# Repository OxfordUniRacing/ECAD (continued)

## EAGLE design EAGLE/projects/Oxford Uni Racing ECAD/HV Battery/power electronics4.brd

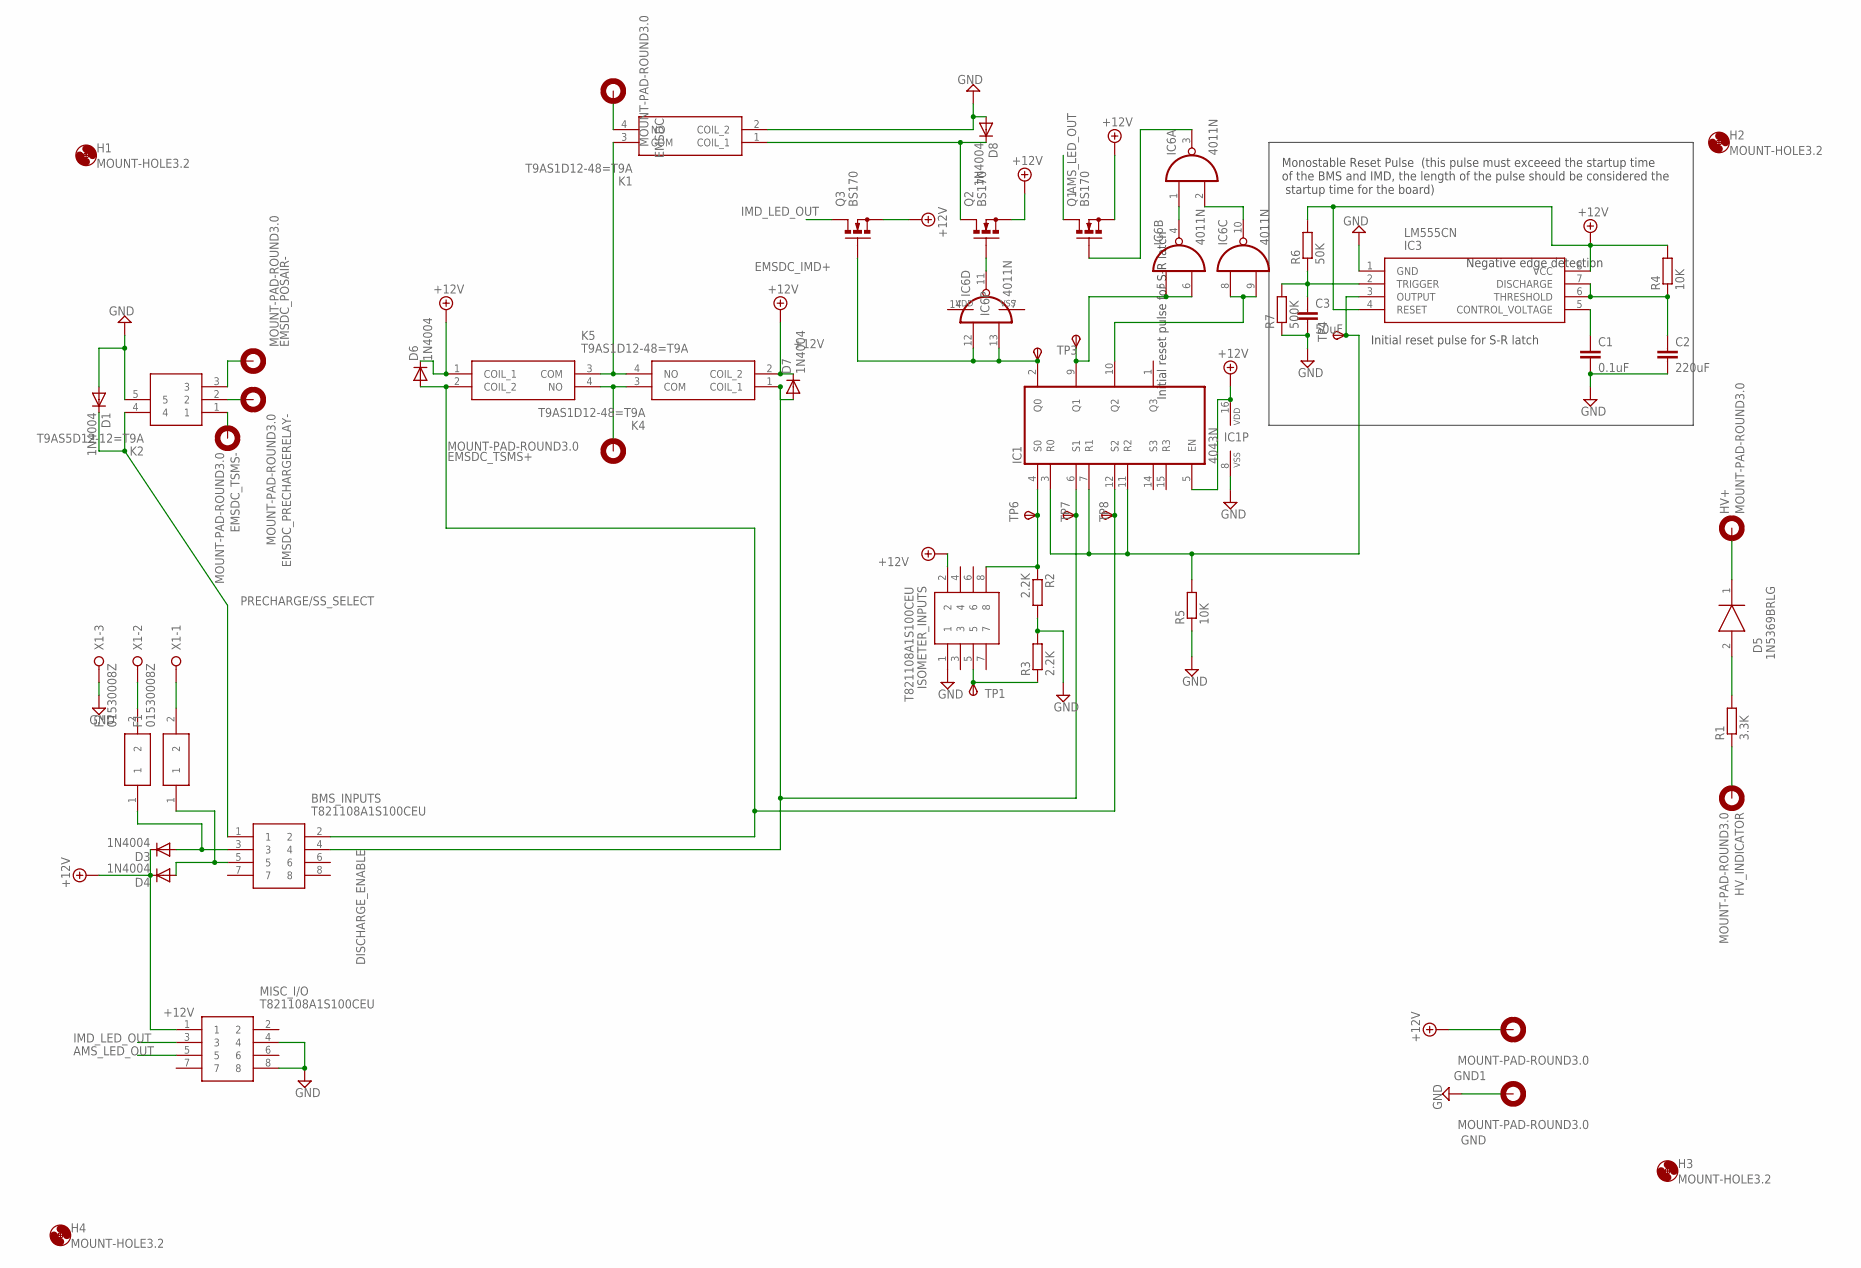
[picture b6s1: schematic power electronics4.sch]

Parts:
BMS_INPUTS: T821108A1S100CEU; HDRV8W64P254_2X4_1778X895X915P
C1: 0.1uF; C050-024X044
C2: 220uF; C050-024X044
C3: 50uF; C050-024X044
D1, D3, D4, D6, D7, D8: 1N4004; DO41-10
D5: 1N5369BRLG; DIOAD2260W109L864D349
EMSDC: MOUNT-PAD-ROUND3.0; 3,0-PAD
EMSDC_POSAIR-: MOUNT-PAD-ROUND3.0; 3,0-PAD
EMSDC_PRECHARGERELAY-: MOUNT-PAD-ROUND3.0; 3,0-PAD
EMSDC_TSMS+: MOUNT-PAD-ROUND3.0; 3,0-PAD
EMSDC_TSMS-: MOUNT-PAD-ROUND3.0; 3,0-PAD
F1, F2: 01530008Z; 01530008
GND, GND1: MOUNT-PAD-ROUND3.0; 3,0-PAD
H1, H2, H3, H4: MOUNT-HOLE3.2; 3,2
HV+: MOUNT-PAD-ROUND3.0; 3,0-PAD
HV_INDICATOR: MOUNT-PAD-ROUND3.0; 3,0-PAD
IC1: 4043N; DIL16
IC3: LM555CN; DIP762W53P254L980H533Q8N
IC6: 4011N; DIL14
ISOMETER_INPUTS: T821108A1S100CEU; HDRV8W64P254_2X4_1778X895X915P
K1, K4, K5: T9AS1D12-48=T9A; T9AS1D1248T9A
K2: T9AS5D12-12=T9A; T9AS1D12
MISC_I/O: T821108A1S100CEU; HDRV8W64P254_2X4_1778X895X915P
Q1, Q2, Q3: BS170; SOT54E
R1: 3.3K; 0207/15
R2, R3: 2.2K; 0207/12
R4, R5: 10K; 0207/15
R6: 50K; 0207/15
R7: 500K; 0207/15
TP1, TP2, TP3, TP4, TP6, TP7, TP8: TPSPAD1-17; P1-17
X1: W237-3E

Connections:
+12V: D3.C, D4.C, D6.C, D7.C, GND1.B3,0, IC1.5 (EN), IC1.16 (VDD), IC3.4 (RESET), IC3.8 (VCC), ISOMETER_INPUTS.2, K4.2 (COIL_2), K5.1 (COIL_1), MISC_I/O.1, Q1.S, Q2.S, Q3.S, R4.2, R6.2
AMS_LED_OUT: MISC_I/O.5, Q1.D
CHG_SAFE: BMS_INPUTS.2, D6.A, IC1.12 (S2), K5.2 (COIL_2), TP8.TP
DISCHARGE_ENABLE: BMS_INPUTS.4, D7.A, IC1.6 (S1), K4.1 (COIL_1), TP7.TP
EMSDC_IMD+: K1.3 (COM), K4.4 (NO), K5.3 (COM)
GND: C1.2, C2.2, C3.2, D1.A, D8.A, GND.B3,0, IC1.8 (VSS), IC3.1 (GND), ISOMETER_INPUTS.1, K1.2 (COIL_2), K2.5, MISC_I/O.4, MISC_I/O.8, R2.2, R3.2, R5.1, R7.1, X1.3
IMD_LED_OUT: MISC_I/O.3, Q3.D
unnamed: EMSDC_TSMS-.B3,0, K2.1
unnamed: EMSDC_POSAIR-.B3,0, K2.3
unnamed: EMSDC_PRECHARGERELAY-.B3,0, K2.2
unnamed: EMSDC_TSMS+.B3,0, K4.3 (COM), K5.4 (NO)
unnamed: D5.1 (K), HV+.B3,0
unnamed: BMS_INPUTS.3, D3.A, F2.1
unnamed: D5.2 (A), R1.2
unnamed: BMS_INPUTS.5, D4.A, F1.1
unnamed: HV_INDICATOR.B3,0, R1.1
unnamed: ISOMETER_INPUTS.5, R3.1, TP1.TP
unnamed: IC1.3 (R0), IC1.7 (R1), IC1.11 (R2), IC3.3 (OUTPUT), R5.2, TP4.TP
unnamed: IC1.9 (Q1), IC6.5 (I0), IC6.6 (I1), TP3.TP
unnamed: IC1.10 (Q2), IC6.8 (I0), IC6.9 (I1)
unnamed: IC6.1 (I0), IC6.4 (O)
unnamed: D8.C, K1.1 (COIL_1), Q2.D
unnamed: EMSDC.B3,0, K1.4 (NO)
unnamed: IC1.4 (S0), ISOMETER_INPUTS.8, R2.1, TP6.TP
unnamed: C2.1, IC3.6 (THRESHOLD), IC3.7 (DISCHARGE), R4.1
unnamed: C1.1, IC3.5 (CONTROL_VOLTAGE)
unnamed: IC6.2 (I1), IC6.10 (O)
unnamed: IC6.3 (O), Q1.G
unnamed: C3.1, IC3.2 (TRIGGER), R6.1, R7.2
unnamed: F2.2, X1.2
unnamed: F1.2, X1.1
unnamed: IC1.2 (Q0), IC6.12 (I0), IC6.13 (I1), Q3.G, TP2.TP
unnamed: IC6.11 (O), Q2.G
PRECHARGE/SS_SELECT: BMS_INPUTS.1, D1.C, K2.4
VDD: IC6.14 (VDD)
VSS: IC6.7 (VSS)

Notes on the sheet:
Negative edge detection
Initial reset pulse for S-R latch
Monostable Reset Pulse (this pulse must exceeed the startup time of the BMS and IMD, the length of the pulse should be considered the startup time for the board)

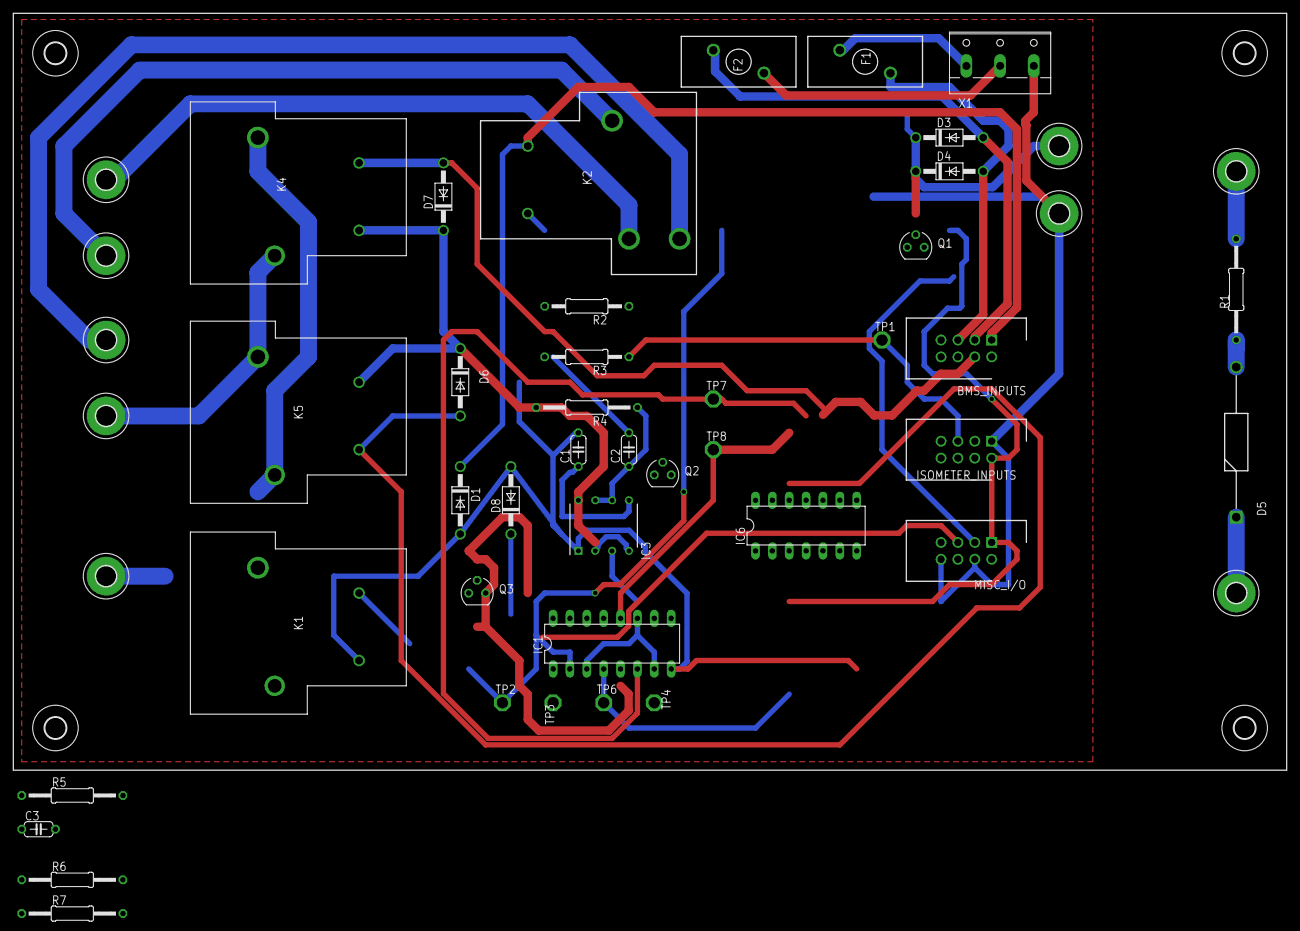
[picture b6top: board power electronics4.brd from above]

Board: 2 copper layers, 191.8 x 114.0 mm, 53 parts (0 on the bottom side), 34 nets.

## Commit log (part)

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2018-12-14 On branch master Initial commit Changes to be committed: new file: cam/DESCRIPTION new file: design blocks/DESCRIPTION new file: design rules/DESCRIPTION new file: design rules/default.dru new file: 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
2018-12-14 On branch master Your branch is up to date with 'origin/master'.
    Changes to be committed:
    new file: EAGLE/cam/DESCRIPTION
    new file: EAGLE/design blocks/DESCRIPTION
    new file: EAGLE/design rules/DESCRIPTION
    new file: EAGLE/design rules/default.dru
    new file: EAGLE/libraries/512-LM2903N-pcb-part-libraries/512-LM2903N-pcb-part-libraries.epw
2018-12-14 On branch master Your branch is up to date with 'origin/master'.
    Changes to be committed:
    deleted: cam/DESCRIPTION
    deleted: design blocks/DESCRIPTION
    deleted: design rules/DESCRIPTION
    deleted: design rules/default.dru
    deleted: libraries/512-LM2903N-pcb-part-libraries/512-LM2903N-pcb-part-libraries.epw
2018-12-15 Backlink to CADLAB.io has been added.
2018-12-15 Start new branch, for AMD/IMS schematic
2018-12-15 addition of libraries and slight update to IMD_AMS_Latch.sch
2018-12-19 Updates to BOTS circuit moving 12v pin to correct position and AMS circuit updates, including library for dual coil relay
2018-12-22 AMS/IMD readme updated
2019-01-03 Schematic and board design of driver switch interlock
2019-01-03 BOTS revision so that ESDC goes through connector
2019-01-03 Add EC2-12NU.epw
2019-01-19 Update for workshop
2019-01-21 general structuring of the project
2019-01-21 imported Driver_TS_Latch and IMS_AMS_Latch
2019-01-21 aded .. in the readme to test for permission to write
2019-01-21 Adding "." to check for permission to write
2019-01-21 adding custom library with the layout of SAME7-XPLD
2019-01-21 removing old projects
2019-01-29 vreated top level schematic
2019-01-30 adding a few forgotten modules to the top level design
2019-01-30 adding mid level design to pedal board
2019-02-02 adding mid level design for wheel board
2019-02-02 adding mid level design for dashboard
2019-02-02 updating top level desing with available data for buttons on the dashboard
2019-02-02 adding mid level design for VCU
2019-02-02 adding the adafruit library as it contains a lot of useful parts
2019-02-02 Change LVMS to TVMS, and add a LVMS to the correct place
2019-02-06 adding desing blocks
2019-02-06 updating mid and high level designs
2019-02-06 adding termination resistor for the CAN to the design block
2019-02-06 added design block for 3.3V regulator
2019-02-06 adding seperate sheets to the low level designs for every design module
2019-02-06 added custom library for CAN tanscever
2019-02-06 adding desing block for CAN transceiver
2019-02-06 adding sheet to the low level desing for all modules, fixing top and mid level desing regarding motor controllers
2019-02-06 added cross sheet wiring for VCU, Pedal board and wheel board
2019-02-06 added cross sheet connections to dashboard
2019-02-09 updated CAN connector with proper pcb connector
2019-02-09 removing wheel board from top level design and marking the wheel board folder obsolete
2019-02-09 added circles for holes on the general pcb layout design block
2019-02-09 added can connector to pedal board, updated descriprion to power delivery
2019-02-09 added power delivery to pedal board
2019-02-09 added throttle connectors
2019-02-09 added outut connectors to the pedal board
2019-02-09 updated CAN connector design block wiring names
2019-02-09 added brake out to pedal board
2019-02-09 added CAN connector to VCU
2019-02-09 added power delivery to VCU
2019-02-09 added motor controller output to VCU
2019-02-09 updated connector names on pedal board
2019-02-09 added op amp to fix voltage of brake pressure sensor
2019-02-13 removed throttle position sensor 3 from all chematics
2019-02-13 added CAN connector to dashboard
2019-02-13 added power delivery to dashboard
2019-02-13 added CAN OUT to dashboard
2019-02-13 added DISPLAY OUT to dashboard
2019-02-13 updated throttle pedal sensor power input to 5V
2019-02-13 removed redundant CAN termination resistor from dashboard
2019-02-13 updated buttons on all levels
2019-02-13 updated resistor values on pedal board
2019-02-15 new BOTS on pedal board with a test copy in Additional
2019-02-15 added final values to pedal board components
2019-02-15 finished SAMC21 blueprint in the custom library
2019-02-15 added microcontroller and relevant connections to pedal board
2019-02-15 added CAN transciever to VCU
2019-02-15 added microcontroller output to a connected to relay to ASS to VCU
2019-02-15 added microcontroller to dashboard
2019-02-15 connected buttons to digital IO pins
2019-02-16 fixed can wiring on VCU
2019-02-16 fixed wiring of TS_Latch on dashboard
2019-02-16 added fuses to boards
2019-02-16 added 1M pullup resistors to analog sensors
2019-02-16 fixed overlapping digital pins
2019-02-20 added indicator LEDs to boards
2019-02-20 added air coil connection on VCU
2019-02-20 added version of samc21 without ext1&2 to the library
2019-02-20 added power pin for air coils
2019-02-20 created basic board layout for dashboard
2019-02-20 added badic pcb layout to pedal board
2019-02-20 added badic pcb layout to VCU
2019-02-23 updated TOP Level Schematic according to recent design changes
2019-02-23 updated MID Level Schematic according to recent design changes
2019-02-23 removed ASS connection of dashboard
2019-02-23 updated VCU with brake lights
2019-02-23 removed brake lights from pedal board
2019-02-23 removed 3.3V regulators from boards, as we will be using the onbloard regulator
2019-02-26 routed board for vcu
2019-02-26 routed board gor pedal board
2019-02-27 added voltage reference
2019-02-27 removed BOTS from pedal board
2019-02-27 fixed some routing issues
2019-02-27 fixed spacing on the blueprint
2019-02-27 added SAME21 without ext 3 as well
2019-02-27 updated microcontroller on pedal board to not incude ext3
2019-02-27 routed dashboard
2019-03-03 added IMD to top level design
2019-03-03 created schematic for IMD
2019-03-03 routed IMD
2019-03-05 fixed IMD with a MOSFET rather than a thyristor
2019-03-05 updated BSPD with a not gate and transistor
2019-03-05 added a resistor to keep the thyristor latched
2019-03-05 removed unnecessary pulldown resistors
2019-03-06 genereted gerber files
2019-03-06 routed pedal board
2019-03-07 added br_press sensor to vcu and replaced fuses
2019-03-07 replaced fuses with correct sized ones
2019-03-07 generated gerber for vcu and pedal board
2019-03-15 Added TS battery, made TSMS last node on ASS, adjusted ports on current sensor and motor controllers, and IMD
2019-03-26 Extended the CAN bus to the batteries
2019-05-08 Added BSPD to VCU sch and ASS two pin screw connector
2019-05-10 7. Disconnect the 5V line from the motor controller output – Done both sch and brd 8. connect the motor controller throttle outputs to ground – Changed on sch not sure if connected up correctly on brd
2019-05-22 not sure why its not commiting
2019-05-25 First iteration of TSAL schematic
2019-05-25 Added name tags to outputs
2019-05-25 Removed unnecessary capacitor from TSAL schematic
2019-05-26 Third iteration of TSAL schematic
    Corrected 555 model, replaced zener clamp with lr8 to reduce wasted current
2019-05-28 Pedal board rerouting
2019-06-02 fixed bspd and switched to smd comparator and AND gates
2019-06-02 replaced resistors with smd
2019-06-02 added RS232 chip to the vcu
2019-06-05 vcu board design done
2019-06-17 owrking on fixing the IMD
2019-07-06 added decoupling capacitors
2019-07-06 fixed ass connections
2019-07-06 fixed RS3232 wiring
2019-07-08 Update to top level design (included cooling pump) Created Control Panel Schematic
2019-07-08 Created Control Panel Board and edited holes lbr so that the name apears on the silkscreen layer
2019-07-09 Completed prelimanary design on control panel board, concerned about size of board
2019-07-10 Control Panel updata
2019-07-11 moved components on schematics to fit printouts and added frames
2019-07-11 small fixes of clearences
2019-07-12 done schematics on IMD
2019-11-11 Add new libary components and first schematic for HV battery board
2019-11-20 added space on vcu for ethernet and usb cable
2019-11-20 added fuse board
2019-11-27 vcu - moved microcontroller down, removed BSPD connector and added a connector for breaklights
2020-01-04 Commiting power electronics files Signed-off-by: Jack Bruford <jack.bruford@oxforduniracing.com>
2020-01-04 rotated labels
2020-01-09 Added positive edge detection for ams relays and leds
2020-02-05 added pdf of sch
2020-02-07 power electronics board final draft (sent to will mathews for approval)
2020-02-07 added wills suggestions and test pads
2020-02-11 vcu silkscreen cleanup
2020-02-11 new vcu gerber generated
2020-02-25 Updated to include discharge/dischare enable bug, amended 555 passive compoenent values to match values in deptartment stores
2020-03-12 created power_electronics8 which is a design for a revised board including mosfets to isolate the 3.3v and 12v rails via charge safe and discharge enable signal nets. Also fixed naming issues with th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
2020-03-14 changes before laptop dies
2020-03-15 Connected TP11 and 12, mods post DRC and ERC, new board layout and rewired CAN to run in parralel
2020-03-16 Made edits as suggested by William Matthews and generated Gerber files
2021-11-17 Did some exporting from eagle
2022-09-09 v2 accumulator main board and module senseboard
2022-09-11 Added instructions for making IBOMs
2022-09-12 Added a .gitignore
2022-09-12 update to gitignore
2022-09-12 Removed EAGLE backup files from git repo
2022-11-09 New Module Sense board
2022-11-11 updated thermister footprint
2022-12-12 New pcb board designed to work with countersink bus bar.
2023-01-18 moved V1.8 accumulator main board gerber files to archive
2023-01-25 Precharge library files and schematic base
2023-01-25 Update to main accumulator board
2023-02-01 New D-sub connectors
2023-02-01 typo
2023-02-06 main board
2023-02-07 added feedback and spaced out sheet 2 slightly
2023-02-08 Precharge for aminah
2023-02-08 Some feedback addressed
2023-02-08 Feedback addressed
2023-02-10 small changes to schematic on acc main board and more feedback
2023-02-11 Updates to precharge schematic
2023-02-15 most of the feedback addressed
2023-02-17 Minor changes to layout added values to RC circuit
2023-02-17 Added feedback
2023-02-17 first precharge brd deisgn,
    need to fix TS/LV separation and add annotation
2023-02-21 Feedback
2023-02-22 Second Precharge board
    Fixes the TS-LV separation and changes from 4 layer board to 2 layer board.
2023-02-22 Removed some testpoints and added a few. Also fixed EMSDC relay path
2023-02-24 Updates to the accumulator main board
2023-02-27 Feedback for precharge board
2023-03-06 Moved a label on nets
2023-03-08 New Main board
    4 layer design, work in progress
2023-03-08 Latching connector
2023-03-08 Main Board - Version 2.1
    Correct dimensions, connectors placed
2023-03-08 Main Board V2.2
    Adds power plane, connects. WIP.
2023-03-21 Main Board V4.1
    Moves some of the IC to the bottom layer. More optimal Connector placement
2023-03-23 Mainboard V4.2
    Wider clearance between wires. Solves DRC errors.
2023-03-28 Library files + new main board/precharge board 8 pin mini-spox connector
2023-03-30 main board schematic update with new connectors
2023-04-05 Mainboard .brd file updates
    Routed all the wires to the connector. and solves DRC conflicts.
2023-04-08 Feedback from Jack 08/04/23
2023-05-29 Mainboard V4.5
    New board layout, 2 layer design. removes circuits for fan and pre-charge.
2023-05-31 Mainboard v5.1
    Fixes the +12V connections
2023-06-02 Final mainboard design
    final mainboard design. v5.1
2023-06-05 Final final mainboard Design (v5.1)
    Adds termination resistors to Can 1. Updates silkscreen. Connects Power plane islands.
    Passes design rule check, verified the CAM files using PCBway gerber viewer
    To do list (if have time):
    change to resettable fuses; add OUR logo (haven't figured out how)
2023-06-08 FINAL FINLAL FINAL mainboard design
    Changes the fuses from car fuses to 2.5A resettable fuses. Adds the OUR logo and designers. Moves LED to more logical locations
